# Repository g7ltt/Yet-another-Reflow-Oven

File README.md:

# Yet another Reflow Oven

http://g7ltt.blogspot.com/2015/03/yet-another-reflow-oven.html

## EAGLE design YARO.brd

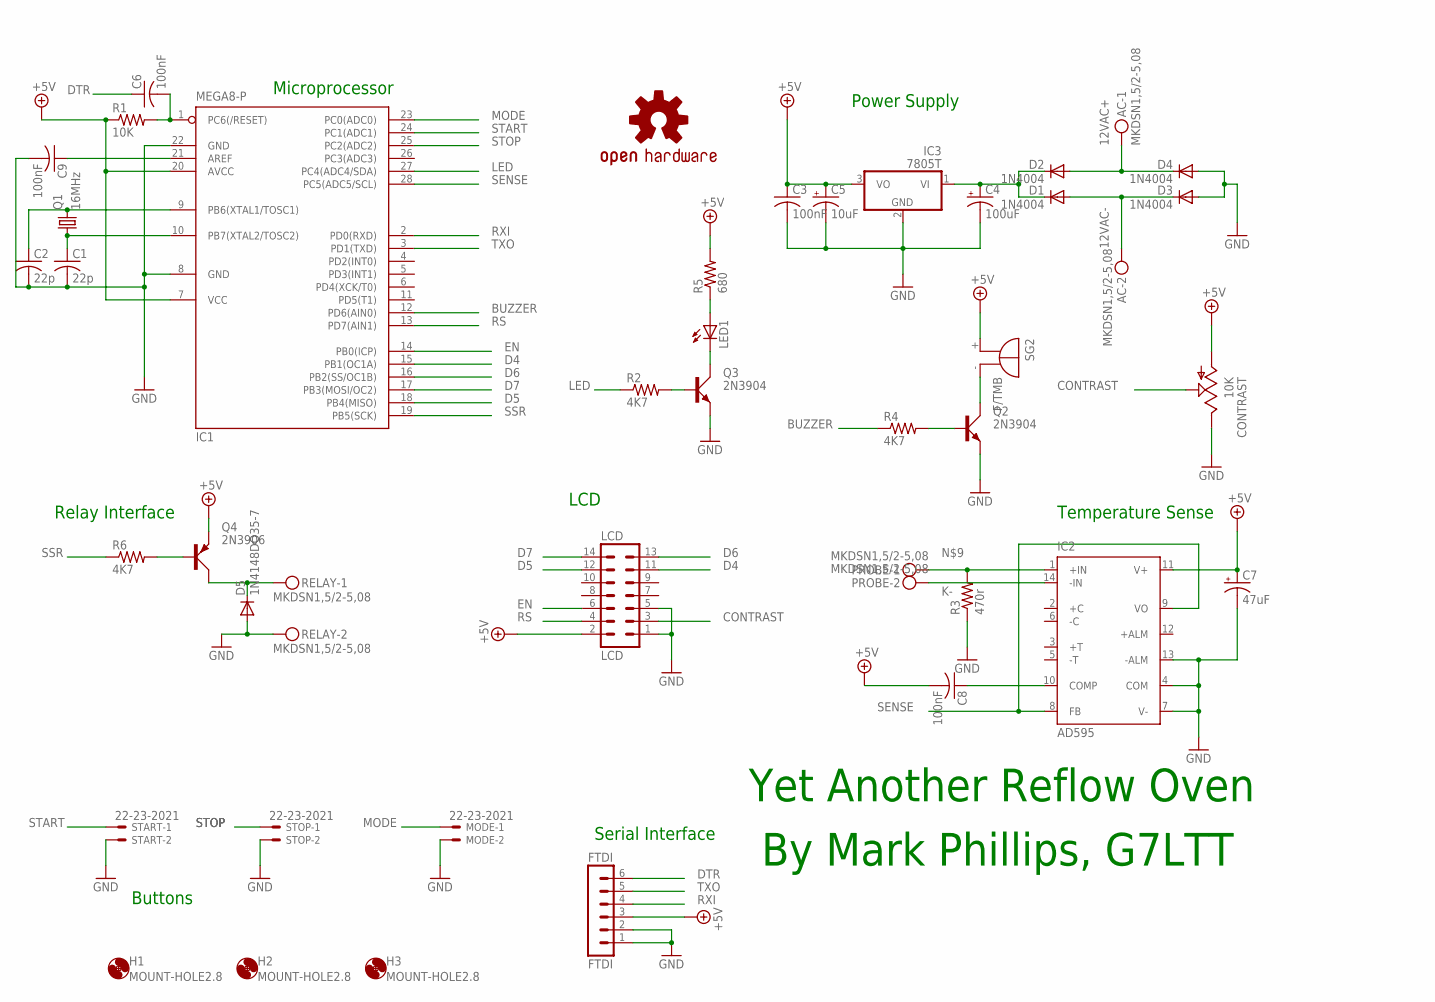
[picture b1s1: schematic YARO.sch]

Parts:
AC: MKDSN1,5/2-5,08
C1, C2: 22p; C025-025X050
C3, C6, C8, C9: 100nF; C025-025X050
C4: 100uF; E2,5-6
C5: 10uF; E2,5-5
C7: 47uF; E2,5-5
CONTRAST: 10K; CA6V
D1, D2, D3, D4: 1N4004; DO41-10
D5: 1N4148DO35-7; DO35-7
FTDI: FTDI; MA06-1
H1, H2, H3: MOUNT-HOLE2.8; 2,8
IC1: MEGA8-P; DIL28-3
IC2: AD595; DIL14
IC3: 7805T; TO220H
LCD: LCD; MA07-2
LED1: LED5MM
LOGO2: OSHW-LOGOL; OSHW-LOGO-L
MODE: 22-23-2021
PROBE: MKDSN1,5/2-5,08
Q1: 16MHz; HC49/S
Q2, Q3: 2N3904; TO92D
Q4: 2N3906; TO92D
R1: 10K; 0204/7
R2, R4, R6: 4K7; 0204/7
R3: 470r; 0204/7
R5: 680; 0204/7
RELAY: MKDSN1,5/2-5,08
SG2: F/TMB
START: 22-23-2021
STOP: 22-23-2021

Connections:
12VAC+: AC.1, D2.A, D4.C
12VAC-: AC.2, D1.A, D3.C
+5V: C3.1, C5.+, C7.+, C8.2, CONTRAST.A, FTDI.3, IC1.7 (VCC), IC1.20 (AVCC), IC2.11 (V+), IC3.3 (VO), LCD.2, Q4.E, R1.1, R5.2, SG2.+
BUZZER: IC1.12 (PD6(AIN0)), R4.1
CONTRAST: CONTRAST.S, LCD.3
D4: IC1.15 (PB1(OC1A)), LCD.11
D5: IC1.18 (PB4(MISO)), LCD.12
D6: IC1.16 (PB2(SS/OC1B)), LCD.13
D7: IC1.17 (PB3(MOSI/OC2)), LCD.14
DTR: C6.1, FTDI.6
EN: IC1.14 (PB0(ICP)), LCD.6
GND: C1.2, C2.2, C3.2, C4.-, C5.-, C7.-, C9.2, CONTRAST.E, D3.A, D4.A, D5.A, FTDI.1, FTDI.2, IC1.8 (GND), IC1.22 (GND), IC2.4 (COM), IC2.7 (V-), IC2.13 (-ALM), IC3.2 (GND), LCD.1, LCD.5, MODE.2, Q2.E, Q3.E, R3.1, RELAY.2, START.2, STOP.2
K-: IC2.14 (-IN), PROBE.2
LED: IC1.27 (PC4(ADC4/SDA)), R2.1
MODE: IC1.23 (PC0(ADC0)), MODE.1
unnamed: C2.1, IC1.9 (PB6(XTAL1/TOSC1)), Q1.2
unnamed: C1.1, IC1.10 (PB7(XTAL2/TOSC2)), Q1.1
unnamed: C4.+, D1.C, D2.C, IC3.1 (VI)
unnamed: C6.2, IC1.1 (PC6(/RESET)), R1.2
unnamed: Q3.B, R2.2
unnamed: LED1.K (C), Q3.C
unnamed: Q4.B, R6.2
unnamed: D5.C, Q4.C, RELAY.1
unnamed: IC2.1 (+IN), PROBE.1, R3.2
unnamed: C9.1, IC1.21 (AREF)
unnamed: C8.1, IC2.10 (COMP)
unnamed: Q2.C, SG2.-
unnamed: Q2.B, R4.2
unnamed: LED1.A, R5.1
RS: IC1.13 (PD7(AIN1)), LCD.4
RXI: FTDI.4, IC1.2 (PD0(RXD))
SENSE: IC1.28 (PC5(ADC5/SCL)), IC2.8 (FB), IC2.9 (VO)
SSR: IC1.19 (PB5(SCK)), R6.1
START: IC1.24 (PC1(ADC1)), START.1
STOP: IC1.25 (PC2(ADC2)), STOP.1
TXO: FTDI.5, IC1.3 (PD1(TXD))

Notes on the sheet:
Yet Another Reflow Oven
By Mark Phillips, G7LTT
Microprocessor
Power Supply
Temperature Sense
LCD
Serial Interface
Buttons
Relay Interface

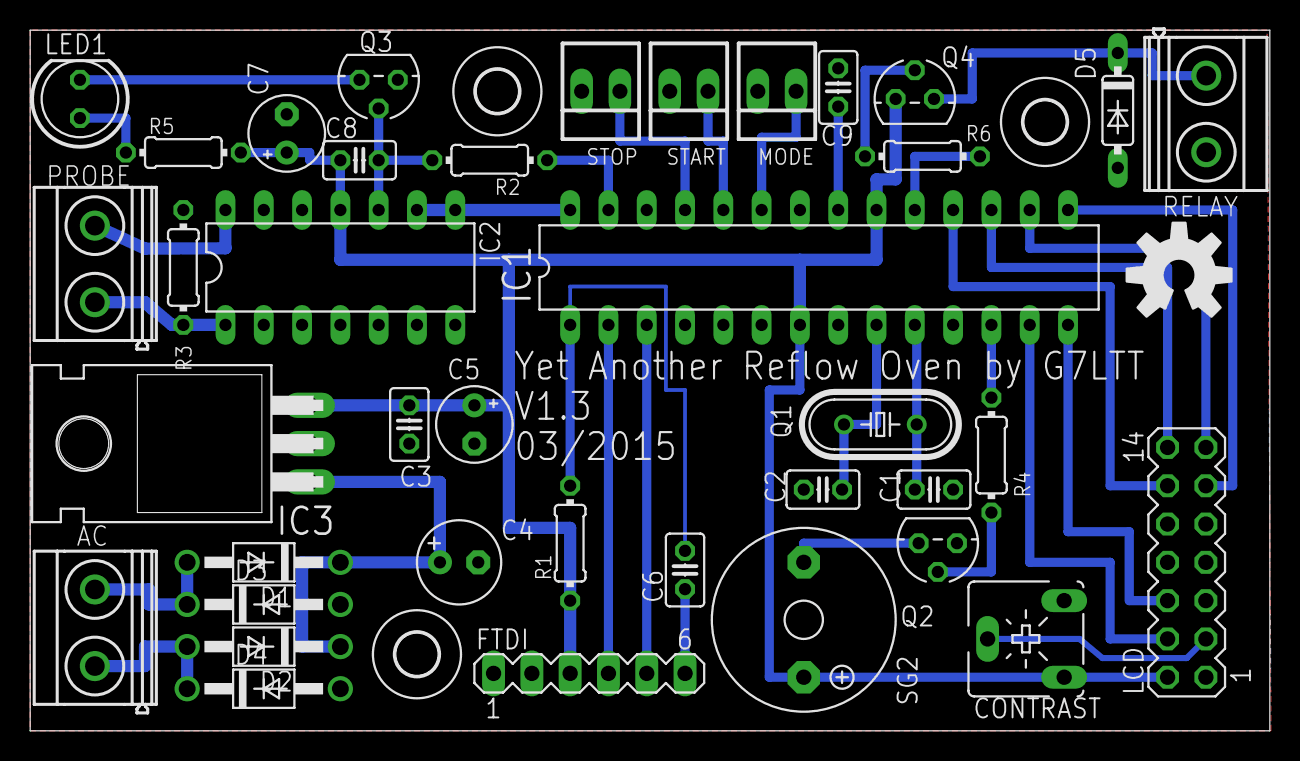
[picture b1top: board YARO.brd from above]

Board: 2 copper layers, 82.2 x 46.5 mm, 42 parts (0 on the bottom side), 36 nets.

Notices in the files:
parts and their libraries:
SparkFun-Aesthetics: Licensing: Creative Commons ShareAlike 4.0 International - https://creativecommons.org/licenses/by-sa/4.0
